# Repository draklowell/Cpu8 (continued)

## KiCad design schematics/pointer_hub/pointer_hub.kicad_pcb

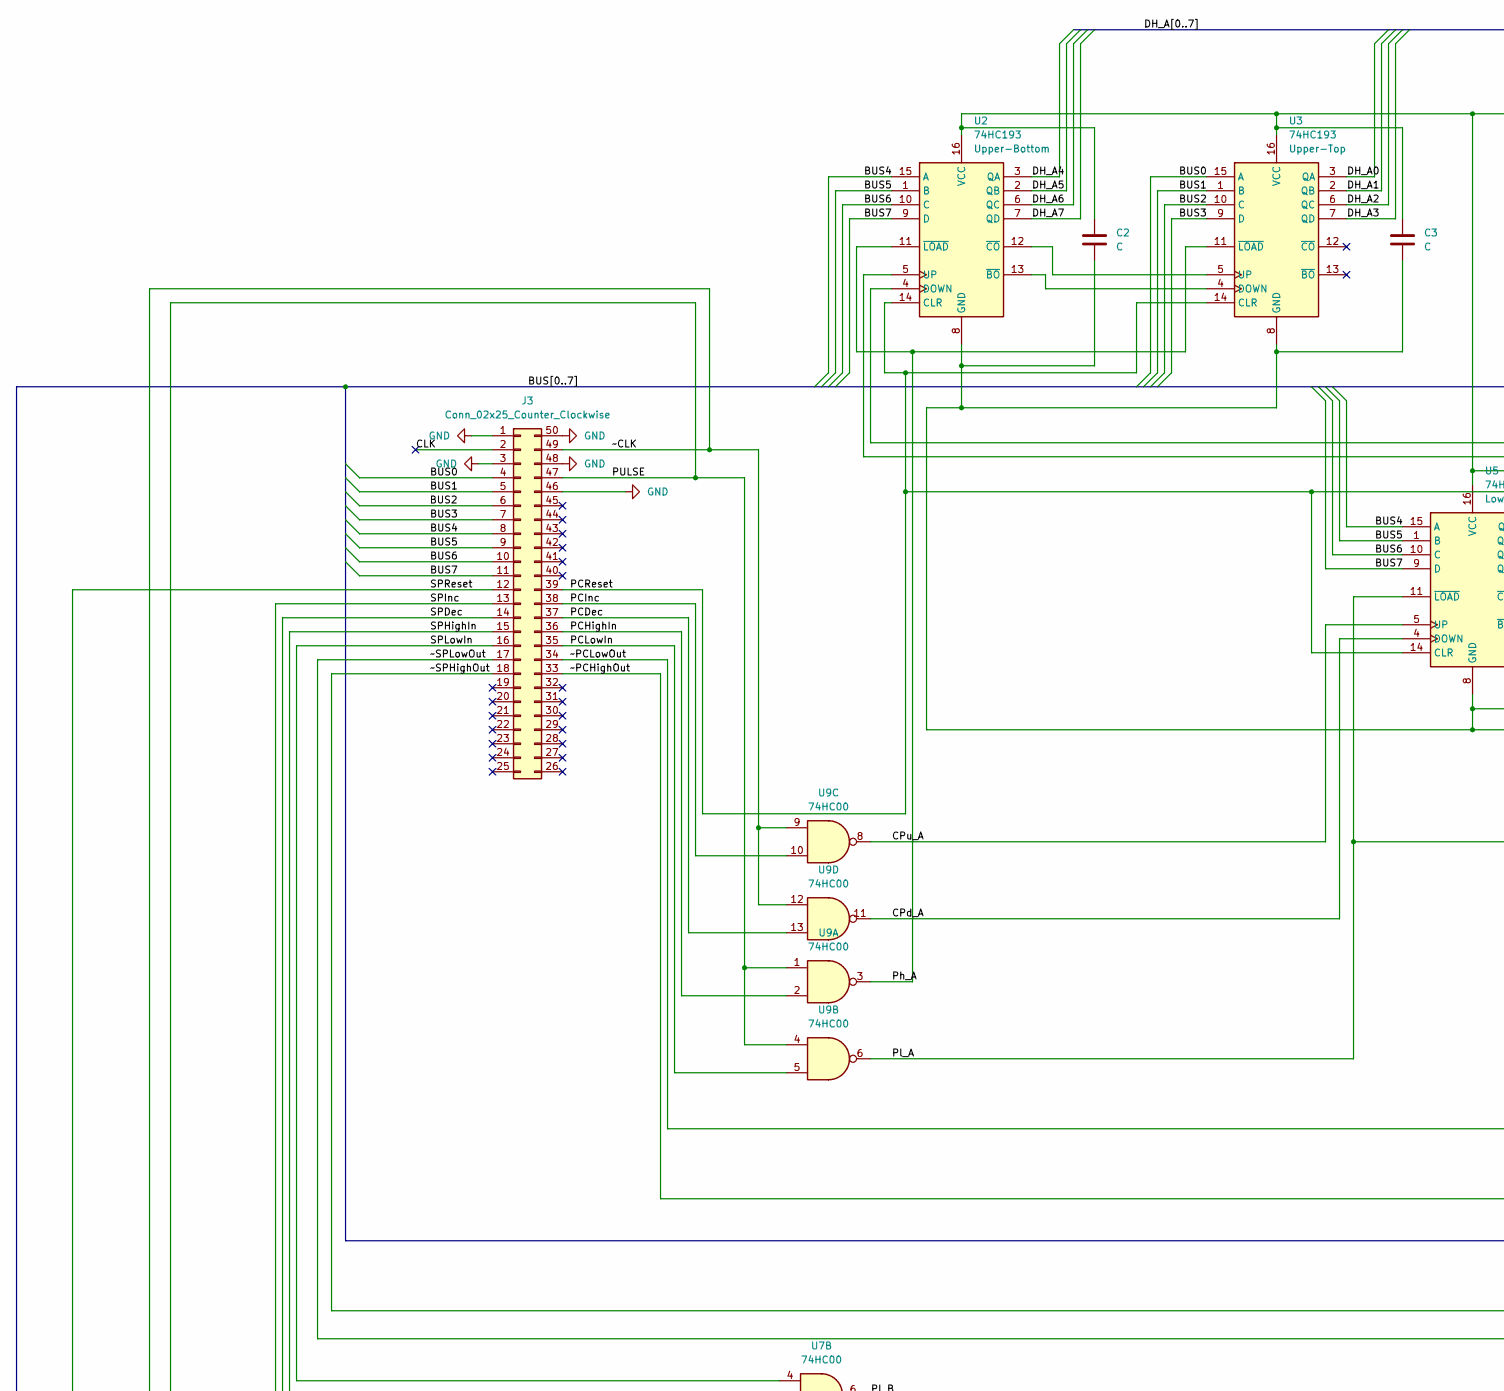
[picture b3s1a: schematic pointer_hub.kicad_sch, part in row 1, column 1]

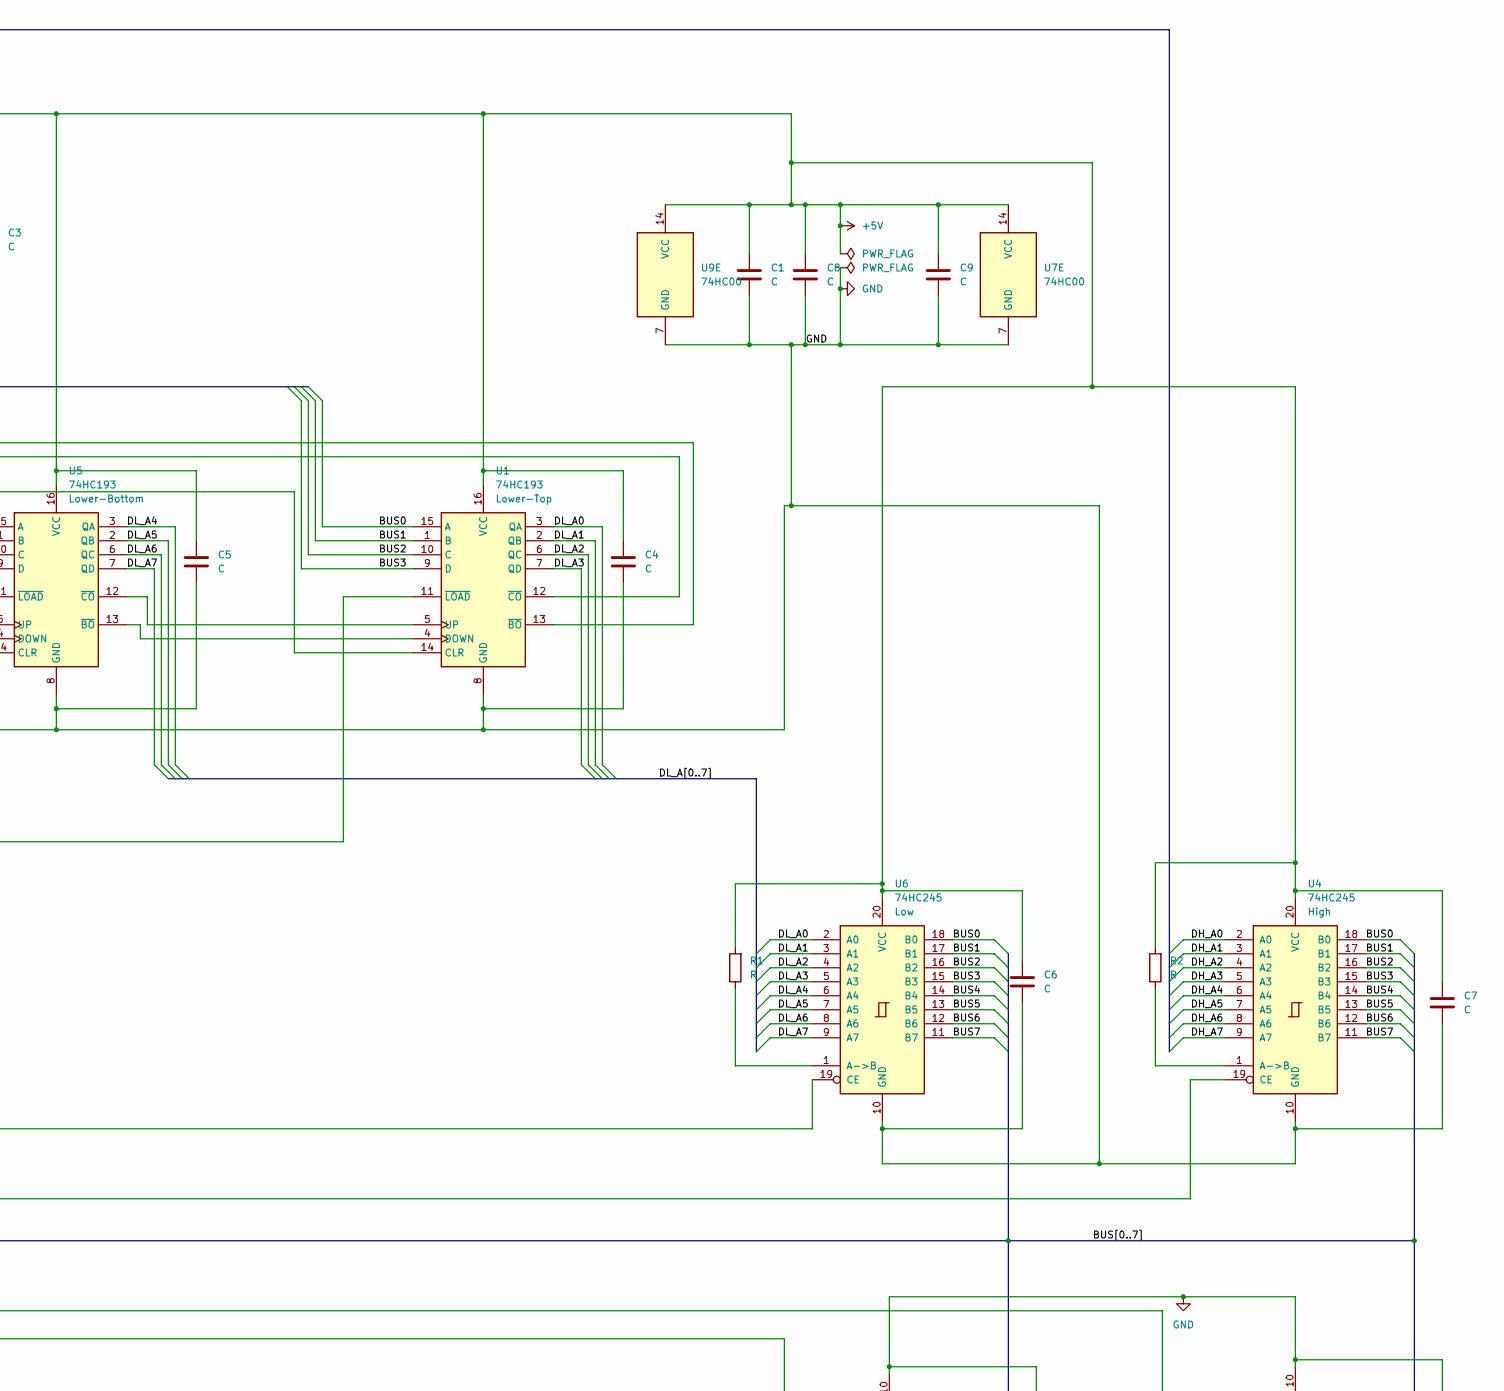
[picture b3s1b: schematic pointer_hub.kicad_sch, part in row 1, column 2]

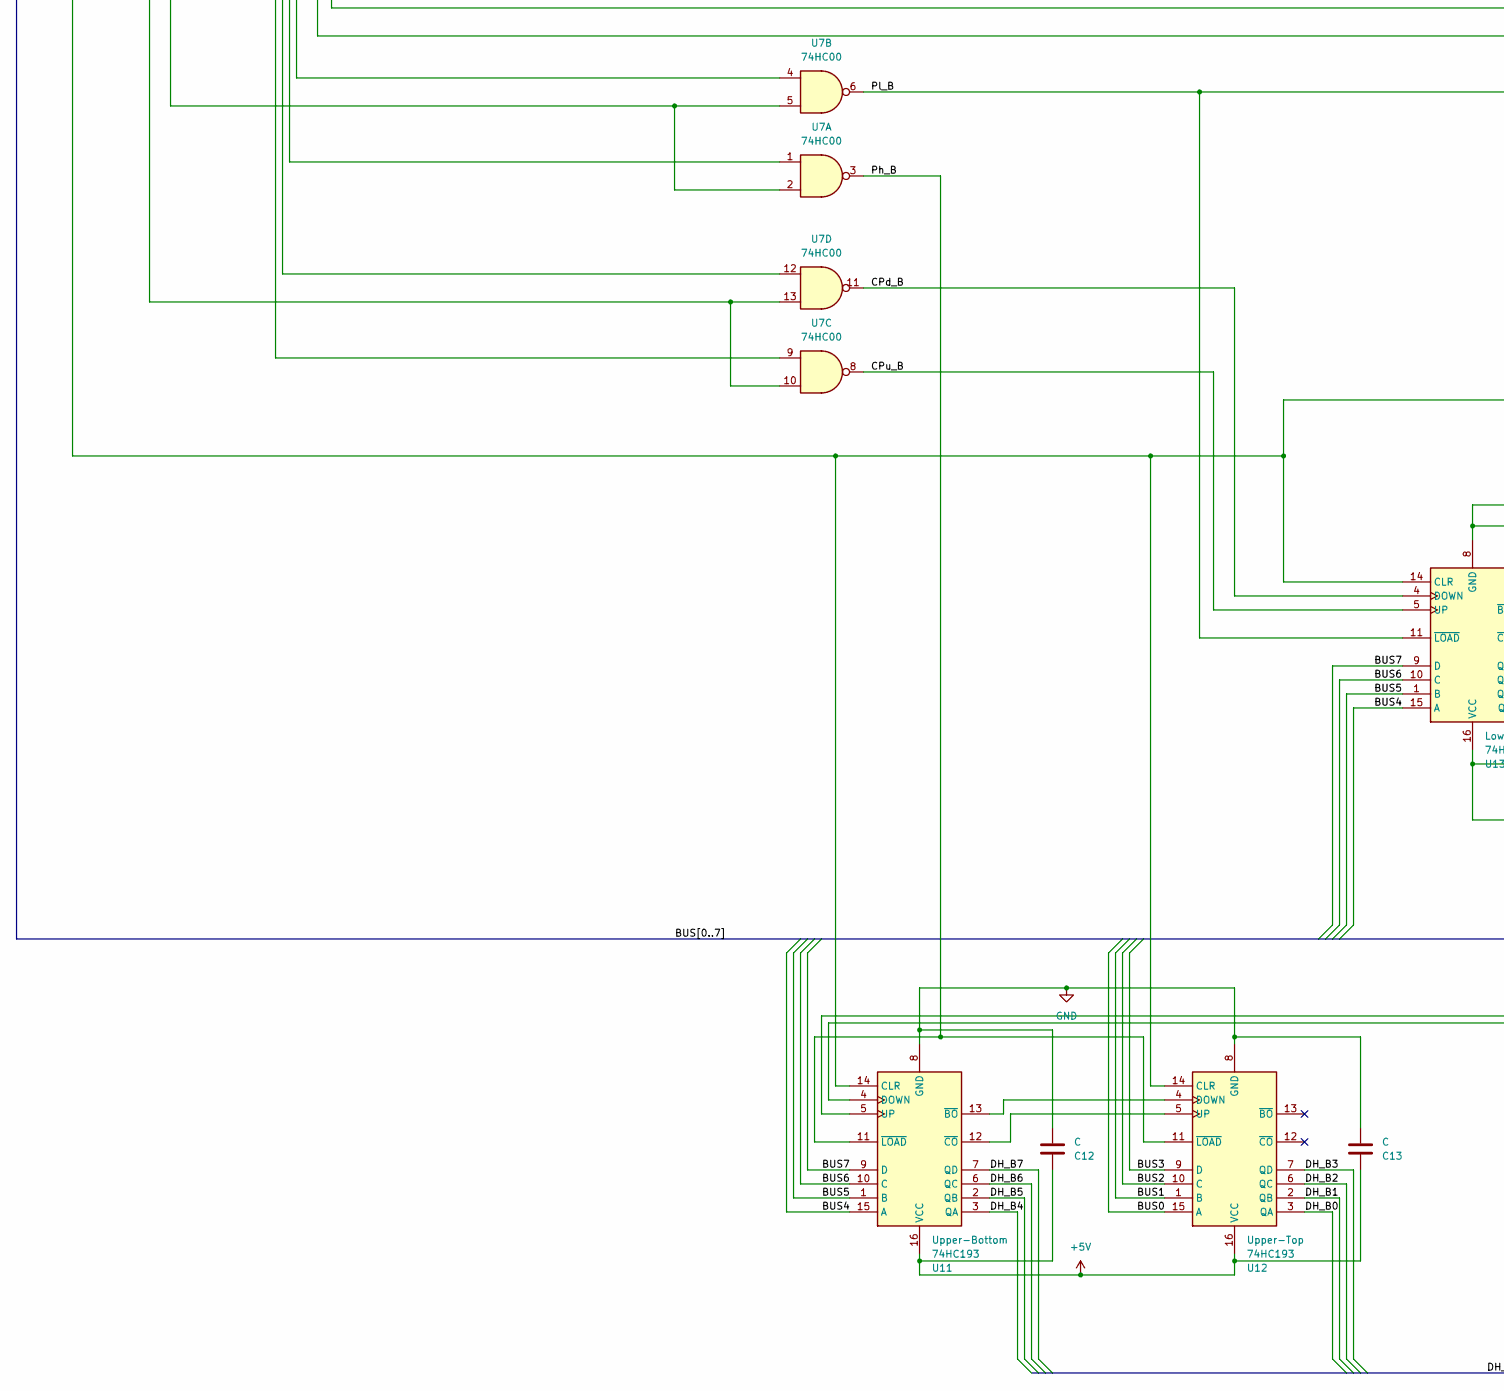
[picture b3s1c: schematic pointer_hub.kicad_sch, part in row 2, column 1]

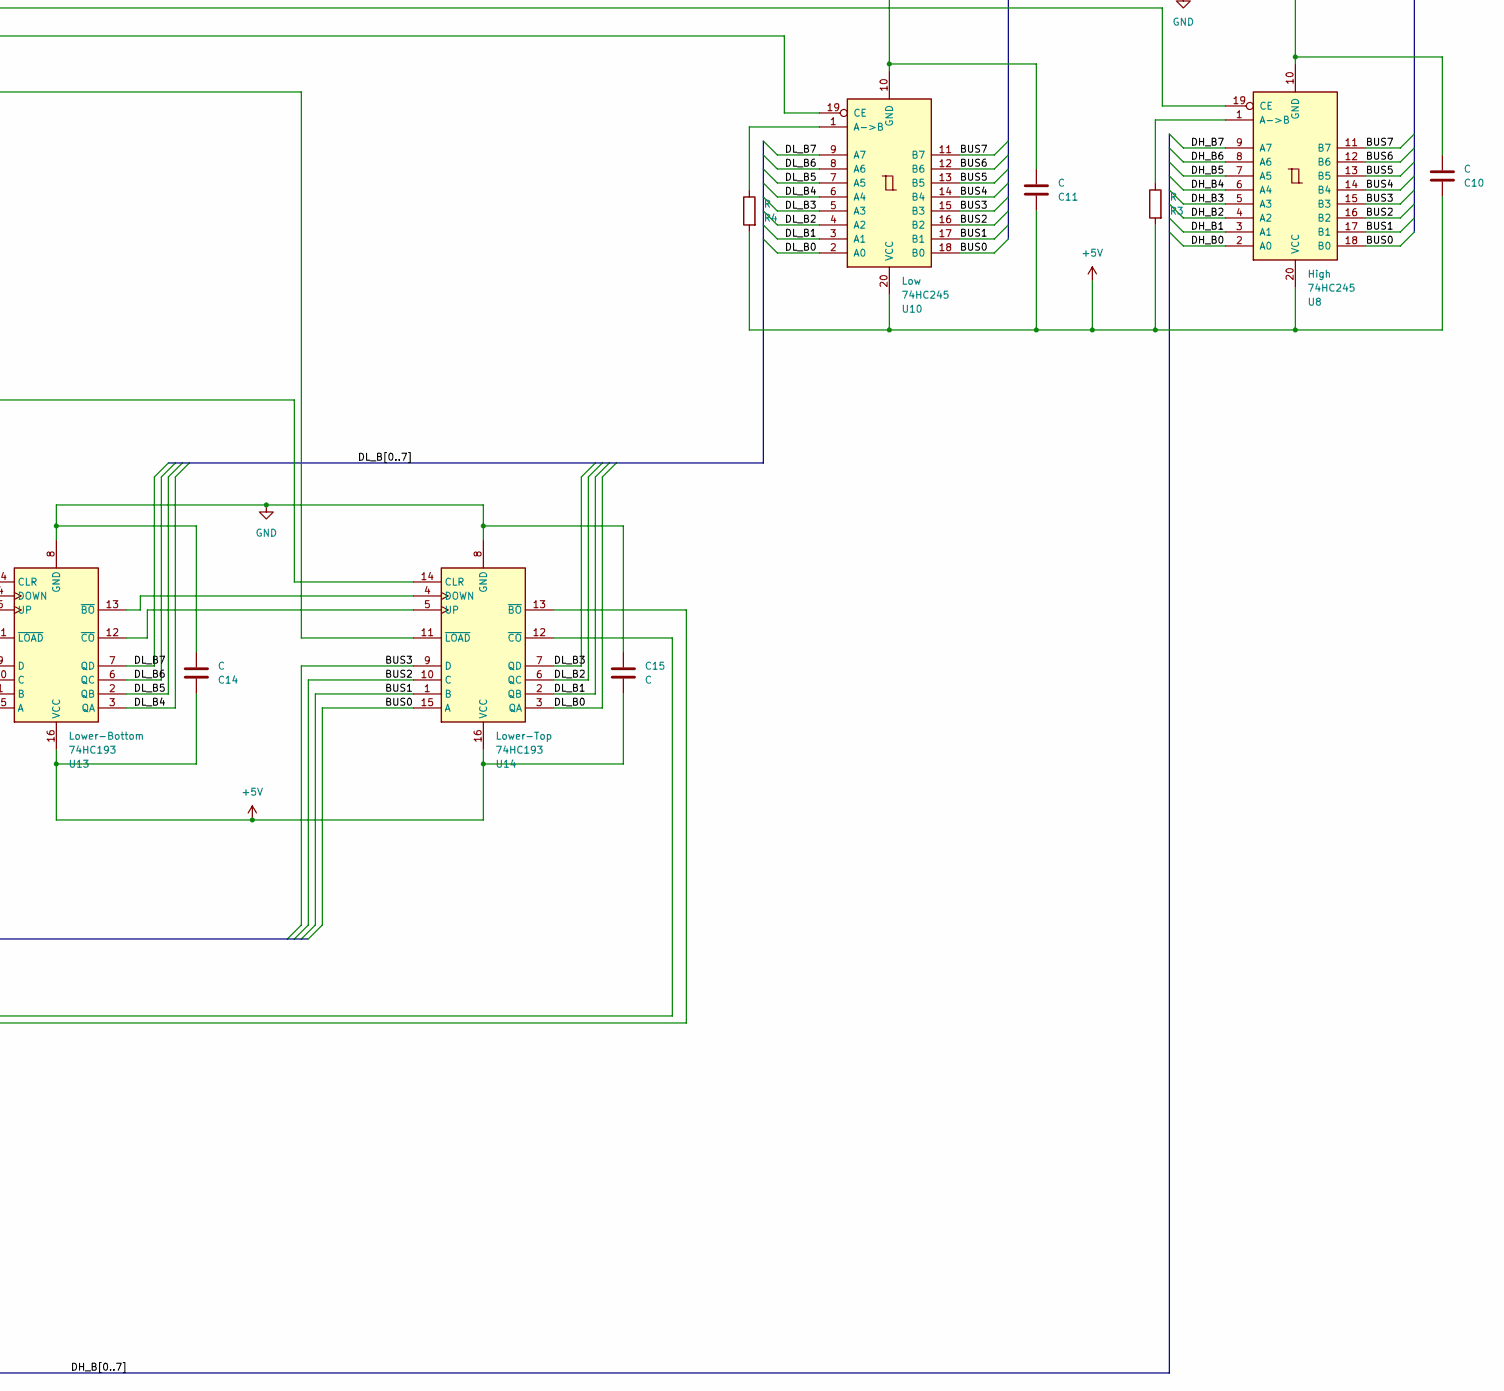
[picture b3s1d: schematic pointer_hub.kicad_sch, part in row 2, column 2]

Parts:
C1, C2, C3, C4, C5, C6, C7, C8, C9, C10, C11, C12, C13, C14, C15: C; CP_Radial_D4.0mm_P1.50mm
J3: Conn_02x25_Counter_Clockwise; Harwin_Gecko-G125-FVX5005L0X_2x25_P1.25mm_Vertical
R1, R2, R3, R4: R; R_Axial_DIN0204_L3.6mm_D1.6mm_P7.62mm_Horizontal
U1, U2, U3, U5, U11, U12, U13, U14: 74HC193; DIP-16_W7.62mm_Socket_LongPads
U4, U6, U8, U10: 74HC245; DIP-20_W7.62mm_Socket_LongPads
U7, U9: 74HC00; SOIC-14_3.9x8.7mm_P1.27mm

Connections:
+5V: C1.1, C2.1, C3.1, C4.1, C5.1, C6.1, C7.1, C8.1, C9.1, C10.1, C11.1, C12.1, C13.1, C14.1, C15.2, R1.2, R2.2, R3.2, R4.2, U1.16 (VCC), U2.16 (VCC), U3.16 (VCC), U4.20 (VCC), U5.16 (VCC), U6.20 (VCC), U7.14 (VCC), U8.20 (VCC), U9.14 (VCC), U10.20 (VCC), U11.16 (VCC), U12.16 (VCC), U13.16 (VCC), U14.16 (VCC)
/BUS0: J3.4, U1.15 (A), U3.15 (A), U4.18 (B0), U6.18 (B0), U8.18 (B0), U10.18 (B0), U12.15 (A), U14.15 (A)
/BUS1: J3.5, U1.1 (B), U3.1 (B), U4.17 (B1), U6.17 (B1), U8.17 (B1), U10.17 (B1), U12.1 (B), U14.1 (B)
/BUS2: J3.6, U1.10 (C), U3.10 (C), U4.16 (B2), U6.16 (B2), U8.16 (B2), U10.16 (B2), U12.10 (C), U14.10 (C)
/BUS3: J3.7, U1.9 (D), U3.9 (D), U4.15 (B3), U6.15 (B3), U8.15 (B3), U10.15 (B3), U12.9 (D), U14.9 (D)
/BUS4: J3.8, U2.15 (A), U4.14 (B4), U5.15 (A), U6.14 (B4), U8.14 (B4), U10.14 (B4), U11.15 (A), U13.15 (A)
/BUS5: J3.9, U2.1 (B), U4.13 (B5), U5.1 (B), U6.13 (B5), U8.13 (B5), U10.13 (B5), U11.1 (B), U13.1 (B)
/BUS6: J3.10, U2.10 (C), U4.12 (B6), U5.10 (C), U6.12 (B6), U8.12 (B6), U10.12 (B6), U11.10 (C), U13.10 (C)
/BUS7: J3.11, U2.9 (D), U4.11 (B7), U5.9 (D), U6.11 (B7), U8.11 (B7), U10.11 (B7), U11.9 (D), U13.9 (D)
/CLK: J3.2
/CPd_A: U5.4 (DOWN), U9.11
/CPd_B: U7.11, U13.4 (DOWN)
/CPu_A: U5.5 (UP), U9.8
/CPu_B: U7.8, U13.5 (UP)
/DH_A0: U3.3 (QA), U4.2 (A0)
/DH_A1: U3.2 (QB), U4.3 (A1)
/DH_A2: U3.6 (QC), U4.4 (A2)
/DH_A3: U3.7 (QD), U4.5 (A3)
/DH_A4: U2.3 (QA), U4.6 (A4)
/DH_A5: U2.2 (QB), U4.7 (A5)
/DH_A6: U2.6 (QC), U4.8 (A6)
/DH_A7: U2.7 (QD), U4.9 (A7)
/DH_B0: U8.2 (A0), U12.3 (QA)
/DH_B1: U8.3 (A1), U12.2 (QB)
/DH_B2: U8.4 (A2), U12.6 (QC)
/DH_B3: U8.5 (A3), U12.7 (QD)
/DH_B4: U8.6 (A4), U11.3 (QA)
/DH_B5: U8.7 (A5), U11.2 (QB)
/DH_B6: U8.8 (A6), U11.6 (QC)
/DH_B7: U8.9 (A7), U11.7 (QD)
/DL_A0: U1.3 (QA), U6.2 (A0)
/DL_A1: U1.2 (QB), U6.3 (A1)
/DL_A2: U1.6 (QC), U6.4 (A2)
/DL_A3: U1.7 (QD), U6.5 (A3)
/DL_A4: U5.3 (QA), U6.6 (A4)
/DL_A5: U5.2 (QB), U6.7 (A5)
/DL_A6: U5.6 (QC), U6.8 (A6)
/DL_A7: U5.7 (QD), U6.9 (A7)
/DL_B0: U10.2 (A0), U14.3 (QA)
/DL_B1: U10.3 (A1), U14.2 (QB)
/DL_B2: U10.4 (A2), U14.6 (QC)
/DL_B3: U10.5 (A3), U14.7 (QD)
/DL_B4: U10.6 (A4), U13.3 (QA)
/DL_B5: U10.7 (A5), U13.2 (QB)
/DL_B6: U10.8 (A6), U13.6 (QC)
/DL_B7: U10.9 (A7), U13.7 (QD)
/PCDec: J3.37, U9.13
/PCHighIn: J3.36, U9.2
/PCInc: J3.38, U9.10
/PCLowIn: J3.35, U9.5
/PCReset: J3.39, U1.14 (CLR), U2.14 (CLR), U3.14 (CLR), U5.14 (CLR)
/PULSE: J3.47, U7.2, U7.5, U9.1, U9.4
/Ph_A: U2.11 (~LOAD), U3.11 (~LOAD), U9.3
/Ph_B: U7.3, U11.11 (~LOAD), U12.11 (~LOAD)
/Pl_A: U1.11 (~LOAD), U5.11 (~LOAD), U9.6
/Pl_B: U7.6, U13.11 (~LOAD), U14.11 (~LOAD)
/SPDec: J3.14, U7.12
/SPHighIn: J3.15, U7.1
/SPInc: J3.13, U7.9
/SPLowIn: J3.16, U7.4
/SPReset: J3.12, U11.14 (CLR), U12.14 (CLR), U13.14 (CLR), U14.14 (CLR)
/~CLK: J3.49, U7.10, U7.13, U9.9, U9.12
/~PСHighOut: J3.33, U4.19 (CE)
/~PСLowOut: J3.34, U6.19 (CE)
/~SPHighOut: J3.18, U8.19 (CE)
/~SPLowOut: J3.17, U10.19 (CE)
GND: C1.2, C2.2, C3.2, C4.2, C5.2, C6.2, C7.2, C8.2, C9.2, C10.2, C11.2, C12.2, C13.2, C14.2, C15.1, J3.1, J3.3, J3.46, J3.48, J3.50, U1.8 (GND), U2.8 (GND), U3.8 (GND), U4.10 (GND), U5.8 (GND), U6.10 (GND), U7.7 (GND), U8.10 (GND), U9.7 (GND), U10.10 (GND), U11.8 (GND), U12.8 (GND), U13.8 (GND), U14.8 (GND)
unnamed: U1.4 (DOWN), U5.13 (~BO)
unnamed: U1.5 (UP), U5.12 (~CO)
unnamed: U1.13 (~BO), U2.4 (DOWN)
unnamed: U1.12 (~CO), U2.5 (UP)
unnamed: U2.13 (~BO), U3.4 (DOWN)
unnamed: U2.12 (~CO), U3.5 (UP)
unnamed: R2.1, U4.1 (A->B)
unnamed: R1.1, U6.1 (A->B)
unnamed: R3.1, U8.1 (A->B)
unnamed: R4.1, U10.1 (A->B)
unnamed: U11.4 (DOWN), U14.13 (~BO)
unnamed: U11.5 (UP), U14.12 (~CO)
unnamed: U11.13 (~BO), U12.4 (DOWN)
unnamed: U11.12 (~CO), U12.5 (UP)
unnamed: U13.13 (~BO), U14.4 (DOWN)
unnamed: U13.12 (~CO), U14.5 (UP)

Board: 2 copper layers, 34 parts (0 on the bottom side), 82 nets, no tracks yet.
